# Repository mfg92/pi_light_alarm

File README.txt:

Install:
  - Flask ( sudo python3 -m pip install Flask)

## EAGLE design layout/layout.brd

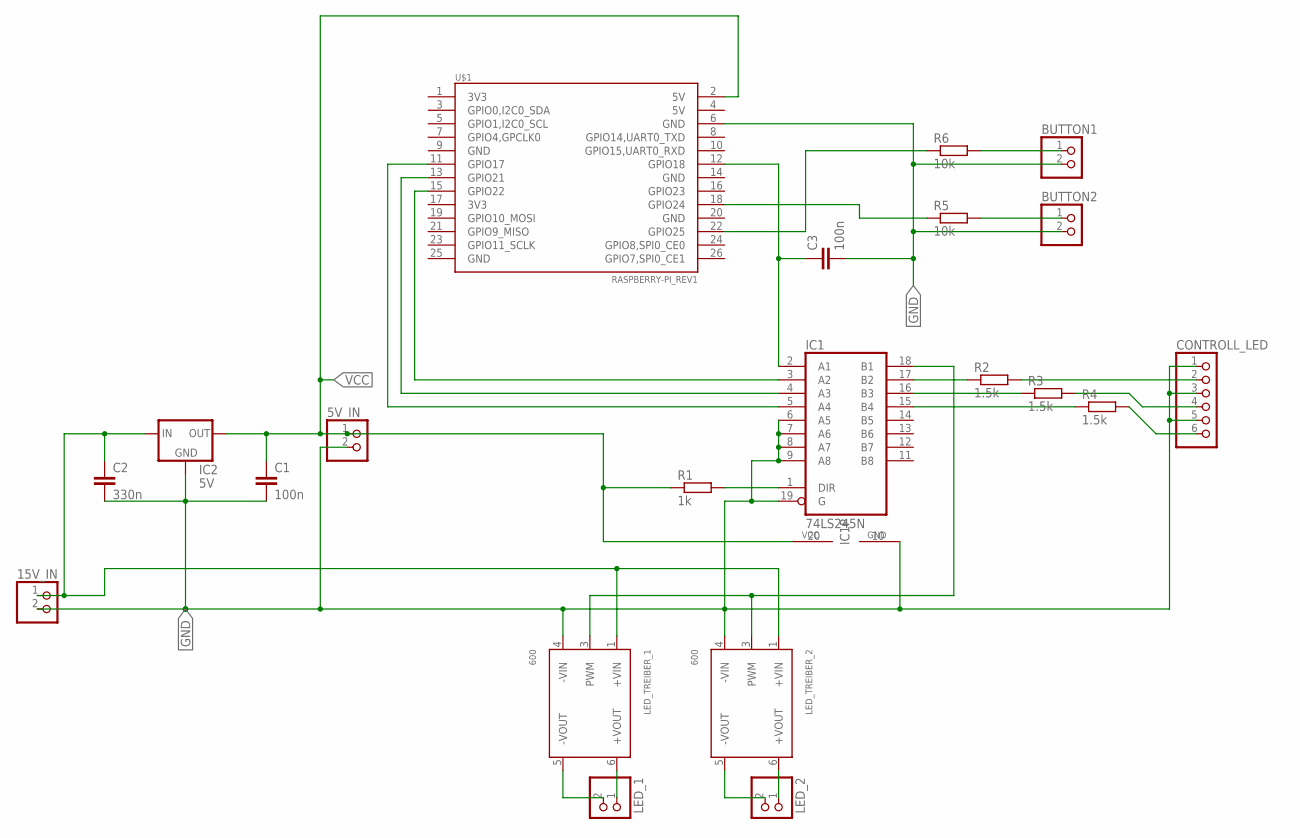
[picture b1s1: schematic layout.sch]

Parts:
5V_IN, 15V_IN: PINHD-1X2; 1X02
BUTTON1, BUTTON2: PINHD-1X2; 1X02
C1, C3: 100n; C7.5B3
C2: 330n; C7.5B5
CONTROLL_LED: PINHD-1X6; 1X06
IC1: 74LS245N; DIL20
IC2: 5V; 78XXS
LED_1, LED_2: PINHD-1X2; 1X02
LED_TREIBER_1, LED_TREIBER_2: 600; LDD-L1
R1: 1k; 0309/10
R2, R3, R4: 1.5k; 0309/10
R5, R6: 10k; 0309/10
U$1: RASPBERRY-PI_REV1

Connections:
GND: 5V_IN.2, 15V_IN.2, BUTTON1.2, BUTTON2.2, C1.2, C2.2, C3.2, CONTROLL_LED.1, CONTROLL_LED.3, CONTROLL_LED.5, IC1.6 (A5), IC1.7 (A6), IC1.8 (A7), IC1.9 (A8), IC1.10 (GND), IC1.19 (G), IC2.GND, LED_TREIBER_1.4 (-VIN), LED_TREIBER_2.4 (-VIN), U$1.6 (GND)
unnamed: LED_1.2, LED_TREIBER_1.5 (-VOUT)
unnamed: LED_1.1, LED_TREIBER_1.6 (+VOUT)
unnamed: LED_2.2, LED_TREIBER_2.5 (-VOUT)
unnamed: LED_2.1, LED_TREIBER_2.6 (+VOUT)
unnamed: IC1.1 (DIR), R1.2
unnamed: 15V_IN.1, C2.1, IC2.IN, LED_TREIBER_1.1 (+VIN), LED_TREIBER_2.1 (+VIN)
unnamed: IC1.18 (B1), LED_TREIBER_1.3 (PWM), LED_TREIBER_2.3 (PWM)
unnamed: C3.1, IC1.2 (A1), U$1.12 (GPIO18)
unnamed: IC1.3 (A2), U$1.15 (GPIO22)
unnamed: IC1.4 (A3), U$1.13 (GPIO21)
unnamed: IC1.5 (A4), U$1.11 (GPIO17)
unnamed: R5.1, U$1.18 (GPIO24)
unnamed: IC1.17 (B2), R2.1
unnamed: IC1.16 (B3), R3.1
unnamed: IC1.15 (B4), R4.1
unnamed: CONTROLL_LED.2, R2.2
unnamed: CONTROLL_LED.4, R3.2
unnamed: CONTROLL_LED.6, R4.2
unnamed: R6.1, U$1.22 (GPIO25)
unnamed: BUTTON2.1, R5.2
unnamed: BUTTON1.1, R6.2
VCC: 5V_IN.1, C1.1, IC1.20 (VCC), IC2.OUT, R1.1, U$1.2 (5V)

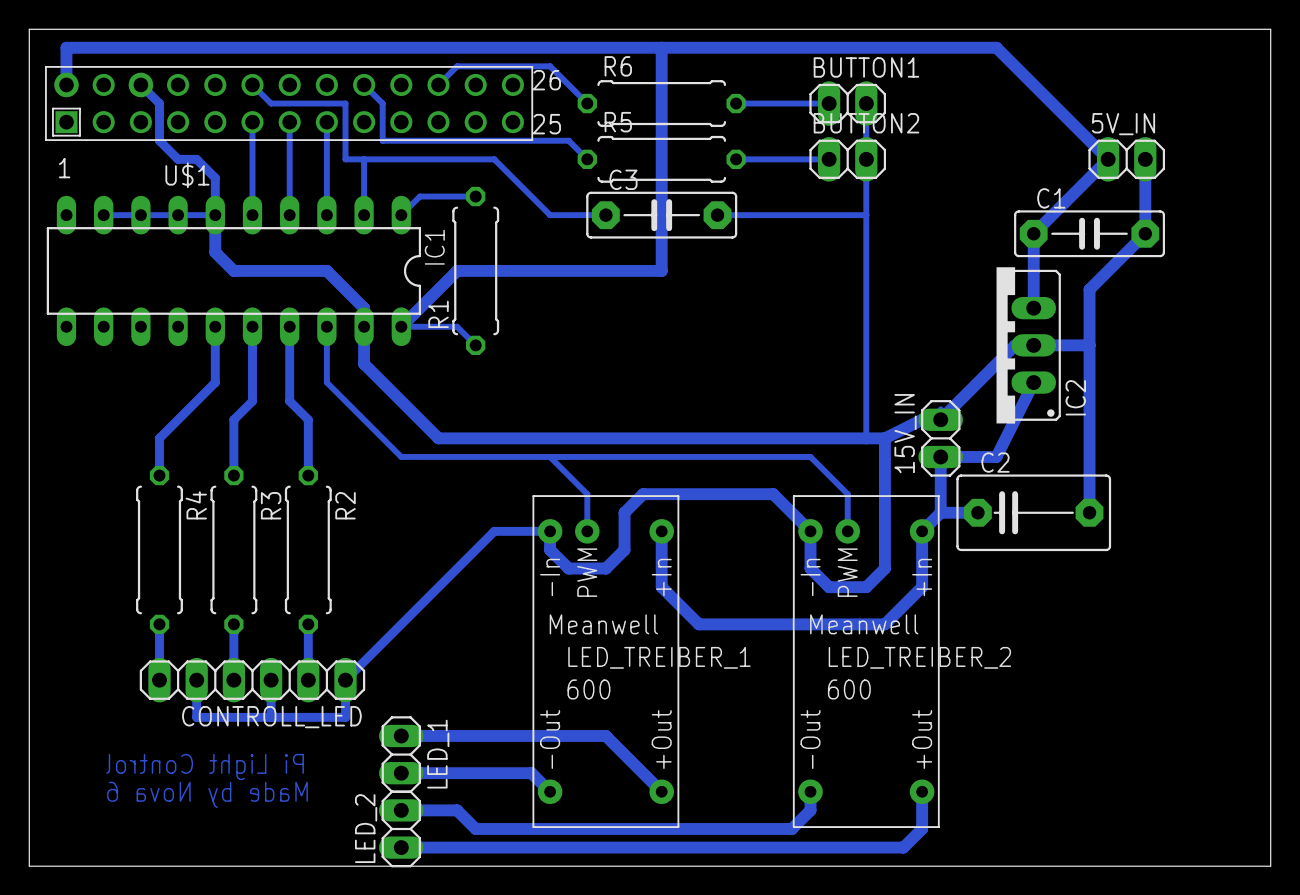
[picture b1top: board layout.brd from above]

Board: 2 copper layers, 84.8 x 57.1 mm, 21 parts (0 on the bottom side), 23 nets.

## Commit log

2016-02-03 light now is default off
2016-02-03 light now is default off #2
2016-02-04 added option to turn light manuel on off or auto
2016-02-05 Added the board layout
